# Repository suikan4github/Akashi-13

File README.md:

# Akashi-13
Ethernet JIG for Nucleo H743ZI2

# Details
This is a LAN9220 ehternet controller board for the Nucleo H743ZI. 

The LAN9220 is accessible through the FMC SRAM configuration NE1. 
The LAN9220 doesn't have READY signal. Thus, the wait cycles should
be set by program appropriately. 

The following signals could be assigned to the interrupt (EXTI).
- PME : PA0
- IRQ : PA4

# Nucleo Pin configurations

The followings are the pin configuration of Nucleo board. 

Also, short bridge have to be configured as the followings : 

- PD8 : Cut SB12 to disconnect the STLINK VCOMM signal. 
- PD9 : Cut SB19 to disconnect the STLINK VCOMM signal. 
- PB6 : Short SB9 to assign LPUART1_TX to STLINK VCOMM signal.
- PB7 : Short SB34 to assign LPUART1_TX to STLINK VCOMM signal.

The USART3 is connected to STLINK VCOMM through the PD8 and PD9 by default. 
These pins are re-assigned to FMC. Thus, the LPUART1 have to be connected
to the STLINK VCOMM through the PB6 and PB7. 

PD6 (FMC_NWAIT) and FMC_NE1 (PC7) are not used in this board. 

# License
This project is licensed by the [MIT license](LICENSE). 

# Gallery

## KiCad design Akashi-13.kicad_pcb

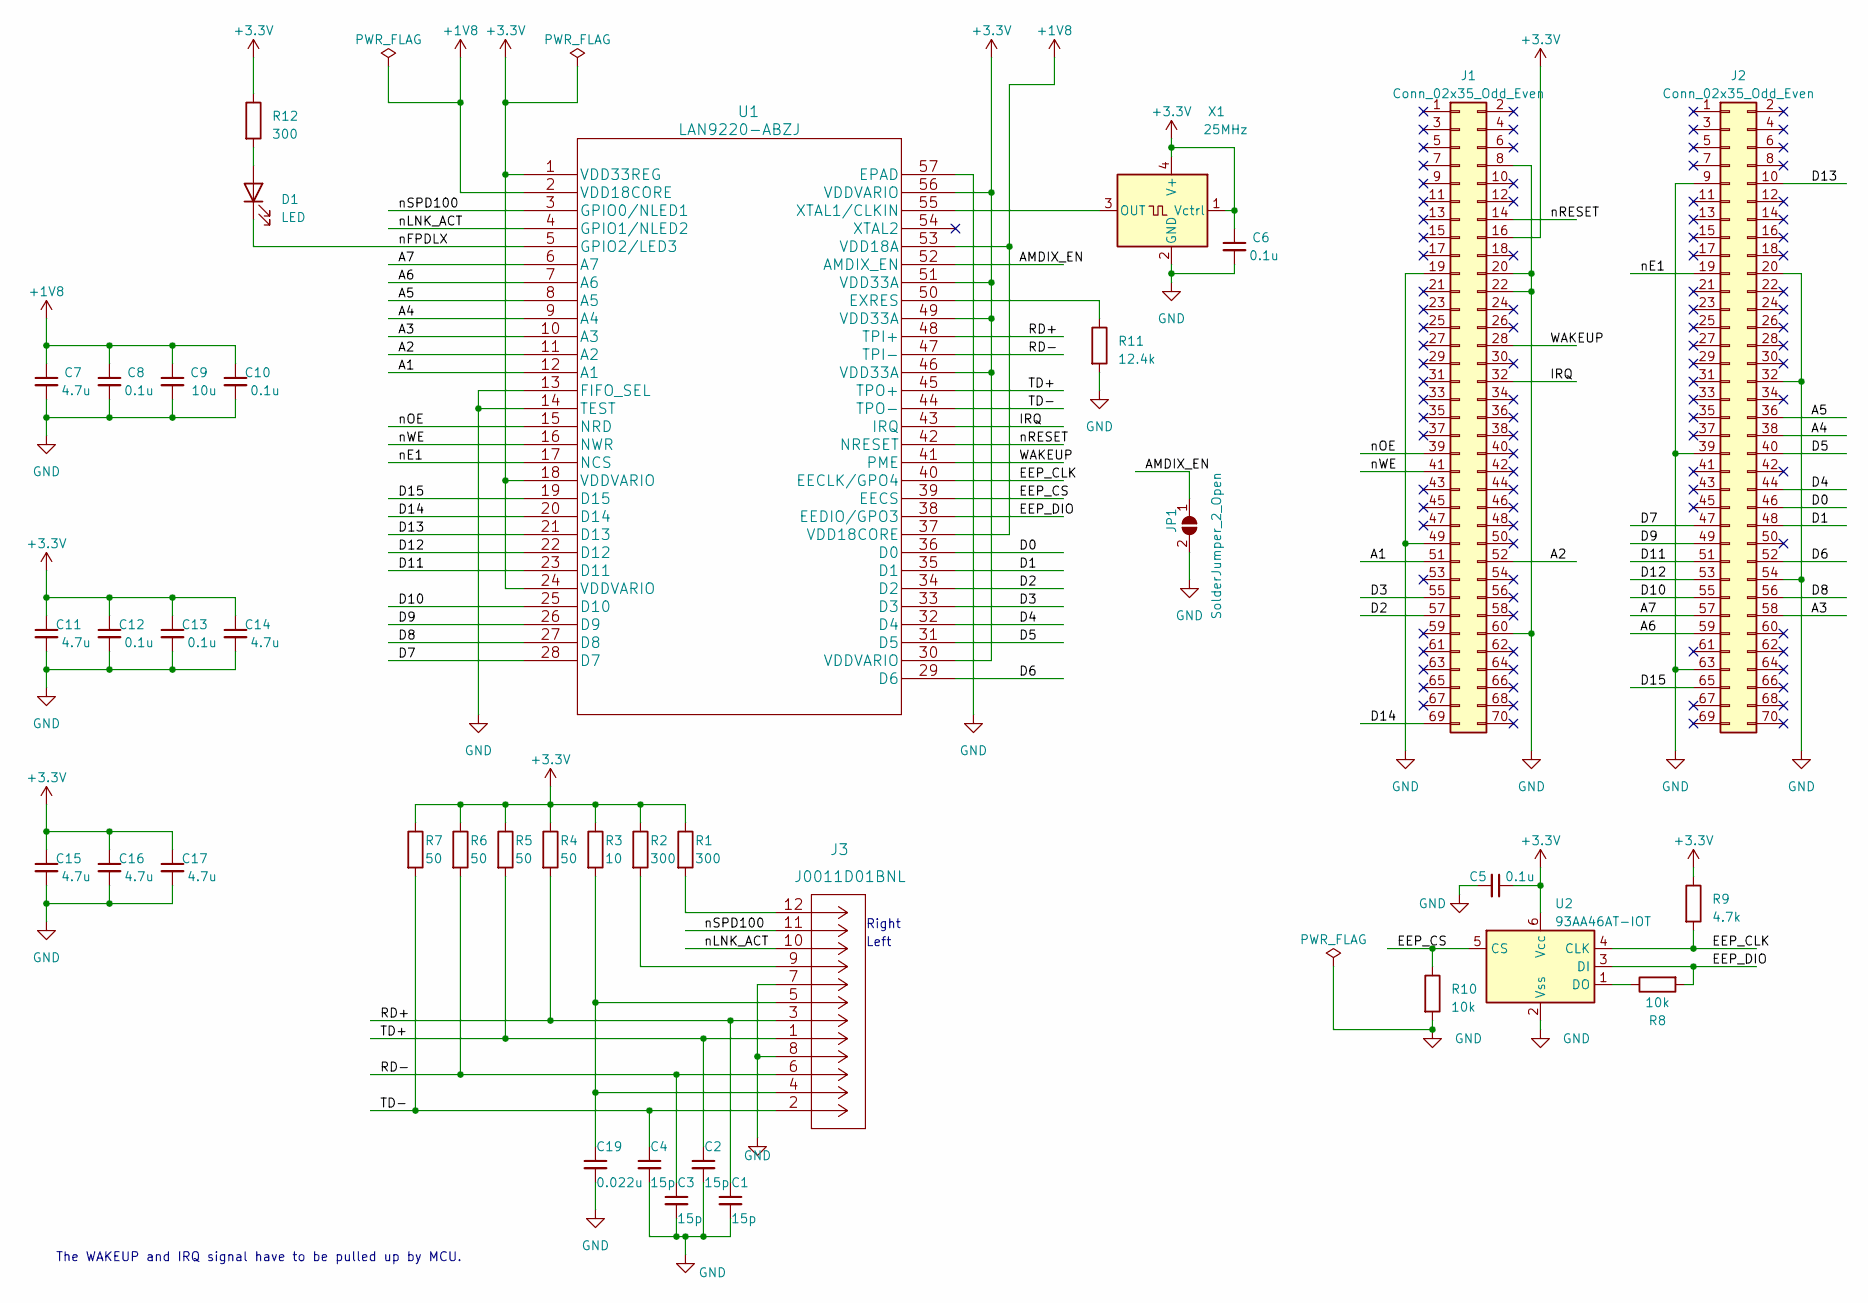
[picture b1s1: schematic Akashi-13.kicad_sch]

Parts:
C1, C2, C3, C4: 15p; C_0603_1608Metric_Pad1.08x0.95mm_HandSolder
C5, C6, C8, C10, C12, C13: 0.1u; C_0603_1608Metric_Pad1.08x0.95mm_HandSolder
C7, C11, C14, C15, C16, C17: 4.7u; C_0603_1608Metric_Pad1.08x0.95mm_HandSolder
C9: 10u; C_0603_1608Metric_Pad1.08x0.95mm_HandSolder
C19: 0.022u; C_0603_1608Metric_Pad1.08x0.95mm_HandSolder
D1: LED; LED_D3.0mm
J1, J2: Conn_02x35_Odd_Even; PinSocket_2x35_P2.54mm_Vertical
J3: J0011D01BNL
JP1: SolderJumper_2_Open; SolderJumper-2_P1.3mm_Open_TrianglePad1.0x1.5mm
R1, R2, R12: 300; R_0603_1608Metric_Pad0.98x0.95mm_HandSolder
R3: 10; R_0603_1608Metric_Pad0.98x0.95mm_HandSolder
R4, R5, R6, R7: 50; R_0603_1608Metric_Pad0.98x0.95mm_HandSolder
R8, R10: 10k; R_0603_1608Metric_Pad0.98x0.95mm_HandSolder
R9: 4.7k; R_0603_1608Metric_Pad0.98x0.95mm_HandSolder
R11: 12.4k; R_0603_1608Metric_Pad0.98x0.95mm_HandSolder
U1: LAN9220-ABZJ; QFN-56-1EP_8x8mm_P0.5mm_EP5.9x5.9mm
U2: 93AA46AT-IOT; SOT-23-6
X1: 25MHz; Oscillator_SMD_Fordahl_DFAS15-4Pin_5.0x3.2mm

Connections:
+1V8: C7.1, C8.1, C9.1, C10.1, U1.2 (VDD18CORE), U1.37 (VDD18CORE), U1.53 (VDD18A)
+3.3V: C5.1, C6.1, C11.1, C12.1, C13.1, C14.1, C15.1, C16.1, C17.1, J1.16, R1.1, R2.1, R3.1, R4.1, R5.1, R6.1, R7.1, R9.1, R12.1, U1.1 (VDD33REG), U1.18 (VDDVARIO), U1.24 (VDDVARIO), U1.30 (VDDVARIO), U1.46 (VDD33A), U1.49 (VDD33A), U1.51 (VDD33A), U1.56 (VDDVARIO), U2.6 (Vcc), X1.1 (Vctrl), X1.4 (V+)
/A1: J1.51, U1.12 (A1)
/A2: J1.52, U1.11 (A2)
/A3: J2.58, U1.10 (A3)
/A4: J2.38, U1.9 (A4)
/A5: J2.36, U1.8 (A5)
/A6: J2.59, U1.7 (A6)
/A7: J2.57, U1.6 (A7)
/AMDIX_EN: JP1.1 (A), U1.52 (AMDIX_EN)
/D0: J2.46, U1.36 (D0)
/D1: J2.48, U1.35 (D1)
/D2: J1.57, U1.34 (D2)
/D3: J1.55, U1.33 (D3)
/D4: J2.44, U1.32 (D4)
/D5: J2.40, U1.31 (D5)
/D6: J2.52, U1.29 (D6)
/D7: J2.47, U1.28 (D7)
/D8: J2.56, U1.27 (D8)
/D9: J2.49, U1.26 (D9)
/D10: J2.55, U1.25 (D10)
/D11: J2.51, U1.23 (D11)
/D12: J2.53, U1.22 (D12)
/D13: J2.10, U1.21 (D13)
/D14: J1.69, U1.20 (D14)
/D15: J2.65, U1.19 (D15)
/EEP_CLK: R9.2, U1.40 (EECLK/GPO4), U2.4 (CLK)
/EEP_CS: R10.1, U1.39 (EECS), U2.5 (CS)
/EEP_DIO: R8.2, U1.38 (EEDIO/GPO3), U2.3 (DI)
/IRQ: J1.32, U1.43 (IRQ)
/RD+: C1.1, J3.3, R4.2, U1.48 (TPI+)
/RD-: C3.1, J3.6, R6.2, U1.47 (TPI-)
/TD+: C2.1, J3.1, R5.2, U1.45 (TPO+)
/TD-: C4.1, J3.2, R7.2, U1.44 (TPO-)
/WAKEUP: J1.28, U1.41 (PME)
/nE1: J2.19, U1.17 (NCS)
/nFPDLX: D1.1 (K), U1.5 (GPIO2/LED3)
/nLNK_ACT: J3.10, U1.4 (GPIO1/NLED2)
/nOE: J1.39, U1.15 (NRD)
/nRESET: J1.14, U1.42 (NRESET)
/nSPD100: J3.11, U1.3 (GPIO0/NLED1)
/nWE: J1.41, U1.16 (NWR)
GND: C1.2, C2.2, C3.2, C4.2, C5.2, C6.2, C7.2, C8.2, C9.2, C10.2, C11.2, C12.2, C13.2, C14.2, C15.2, C16.2, C17.2, C19.2, J1.8, J1.19, J1.20, J1.22, J1.49, J1.60, J2.9, J2.20, J2.32, J2.39, J2.54, J2.63, J3.7, J3.8, J3.15, J3.16, JP1.2 (B), R10.2, R11.2, U1.13 (FIFO_SEL), U1.14 (TEST), U1.57 (EPAD), U2.2 (Vss), X1.2 (GND)
unnamed: C19.1, J3.4, J3.5, R3.2
unnamed: D1.2 (A), R12.2
unnamed: J3.9, R2.2
unnamed: J3.12, R1.2
unnamed: R11.1, U1.50 (EXRES)
unnamed: U1.55 (XTAL1/CLKIN), X1.3 (OUT)
unnamed: R8.1, U2.1 (DO)

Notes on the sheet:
Right
The WAKEUP and IRQ signal have to be pulled up by MCU.
Left

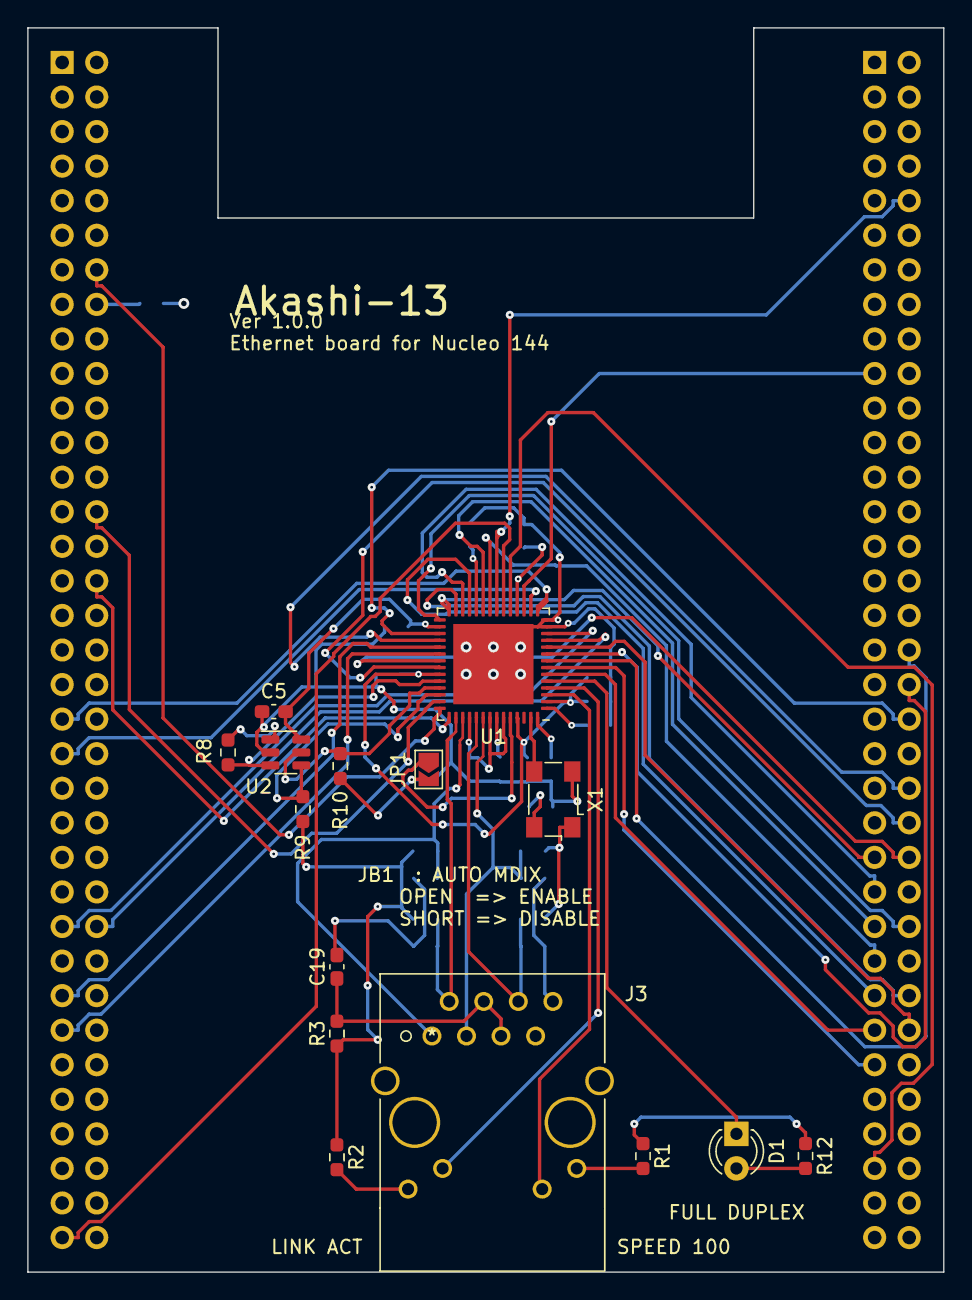
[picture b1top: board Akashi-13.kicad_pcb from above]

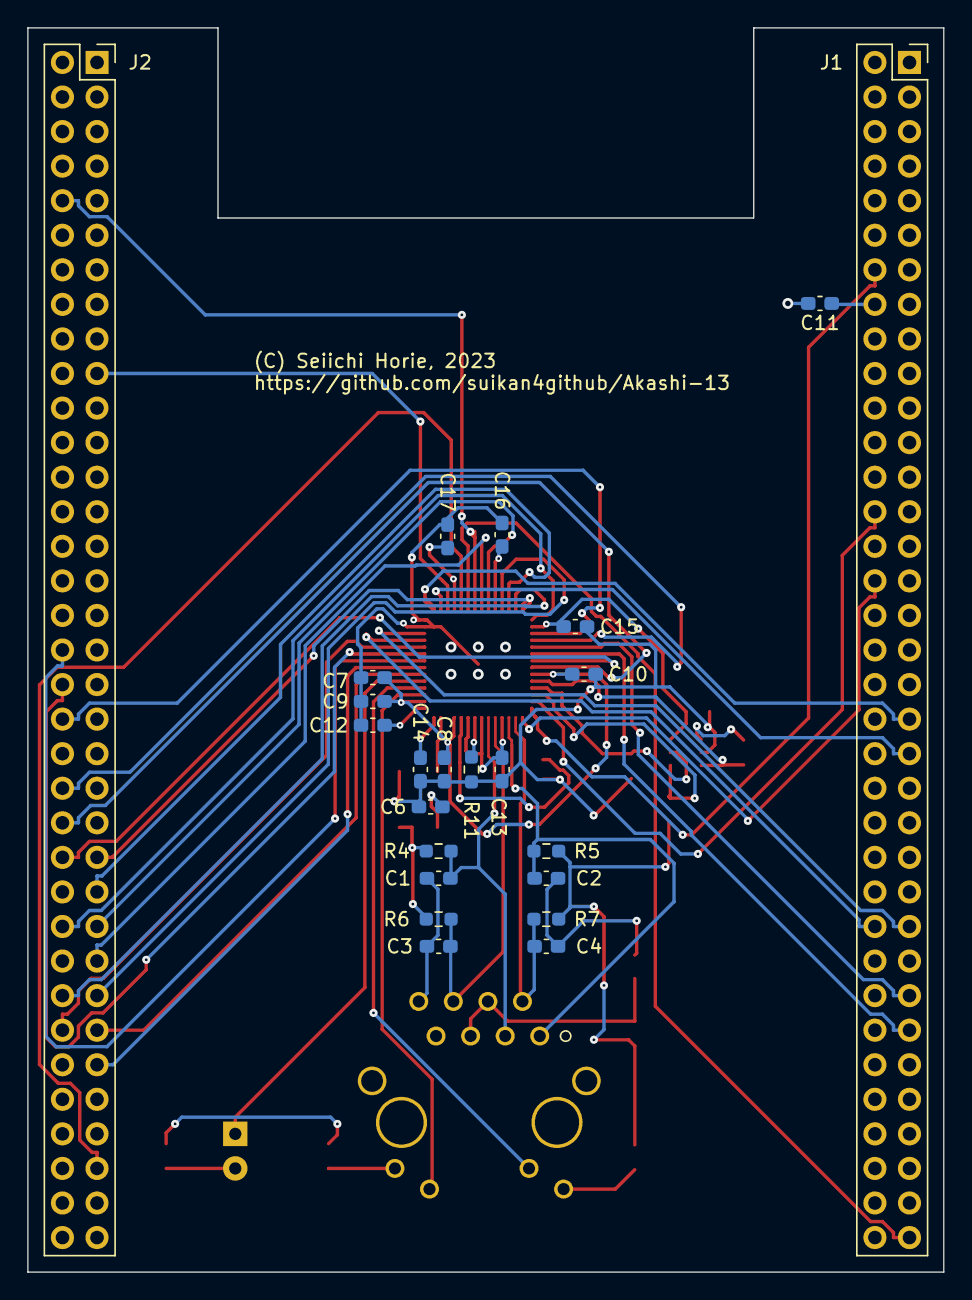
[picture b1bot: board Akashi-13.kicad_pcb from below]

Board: 4 copper layers, 67.3 x 91.4 mm, 38 parts (23 on the bottom side), 50 nets.

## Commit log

2023-03-21 Drawing schematics.
    Done round the RF-45 connectors.
    Connecting the power of the LAN9220.
2023-03-21 Added EEPROM
2023-03-23 ST Link VCOM changed. IRQ/WAKE UP changed.
    ST LINK vcom are moved from USART3 to LPUART1
    Now, we don't need extra wireling.
    Alternatively, short bridged of the baord have to be modified.
    IQR/WAKEUP pins are moved. Now. we can cut two extra pins of
    morpho connectors to reduce the pin force.
2023-03-23 Finished to input schematics.
    ERC OK.
2023-03-23 All bypass chapacitor of LAN9220 and XTAL are placed.
2023-03-24 Placed all parts
2023-03-24 Fixed wrong courtyard of the J3.
    Ready to autoroute.
2023-03-24 in the middle of routing
2023-03-25 Layout done.
2023-03-25 Set shield pins of the Mojular Jack to GND.
2023-03-25 Add comment on the board.
    JB1
    LEDs
2023-03-26 Write README.
2023-03-26 Print the schematics and Gerber.
2023-04-09 Add vias to the exposed pad of U1.
    Also following FusionPCB rules.
2023-04-09 Add version number to sylkscreen
2023-04-09 Refined README.
2023-04-09 Add board 3D view.

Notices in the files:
parts and their libraries:
Copyright 2021 Accelerated Designs. All rights reserved.
